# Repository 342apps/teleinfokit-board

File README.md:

# teleinfokit-board

## Firmware TeleInfoKit

Ce repo comprend les fichiers source Eagle, schema et PCB pour le module de collecte de tele-information [Teleinfokit](https://342apps.net/module-teleinfokit/) associé à son [firmware dédié](https://github.com/342apps/teleinfokit).

Ce module permet de récupérer les données de consommation électrique grâce aux données de télé-information du bus TIC des compteurs électriques français et d'exploiter ces données dans une application de domotique telle que Home Assistant.

## Compatibilité avec ESPHome

Ce module est également compatible avec un firmware généré par [ESPHome](https://esphome.io/) pour une integration dans Home Assistant. 

Le fichier de configuration compatible avec ce module ainsi que toute la documentation est disponible dans le dossier [esphome](./esphome/). Ce firmware offre cependant moins de fonctionnalités que le firmware natif.

## PCB

Fichier source [schematics Eagle](eagle/v4/schematics.sch)

Les versions hardware 3 et 4 sont disponibles dans leurs [répertoires dédiés](/eagle/).

### Gerber files

Toutes les ressources de production générées par Eagle sont dans le dossier [CAMOutputs](CAMOutputs).

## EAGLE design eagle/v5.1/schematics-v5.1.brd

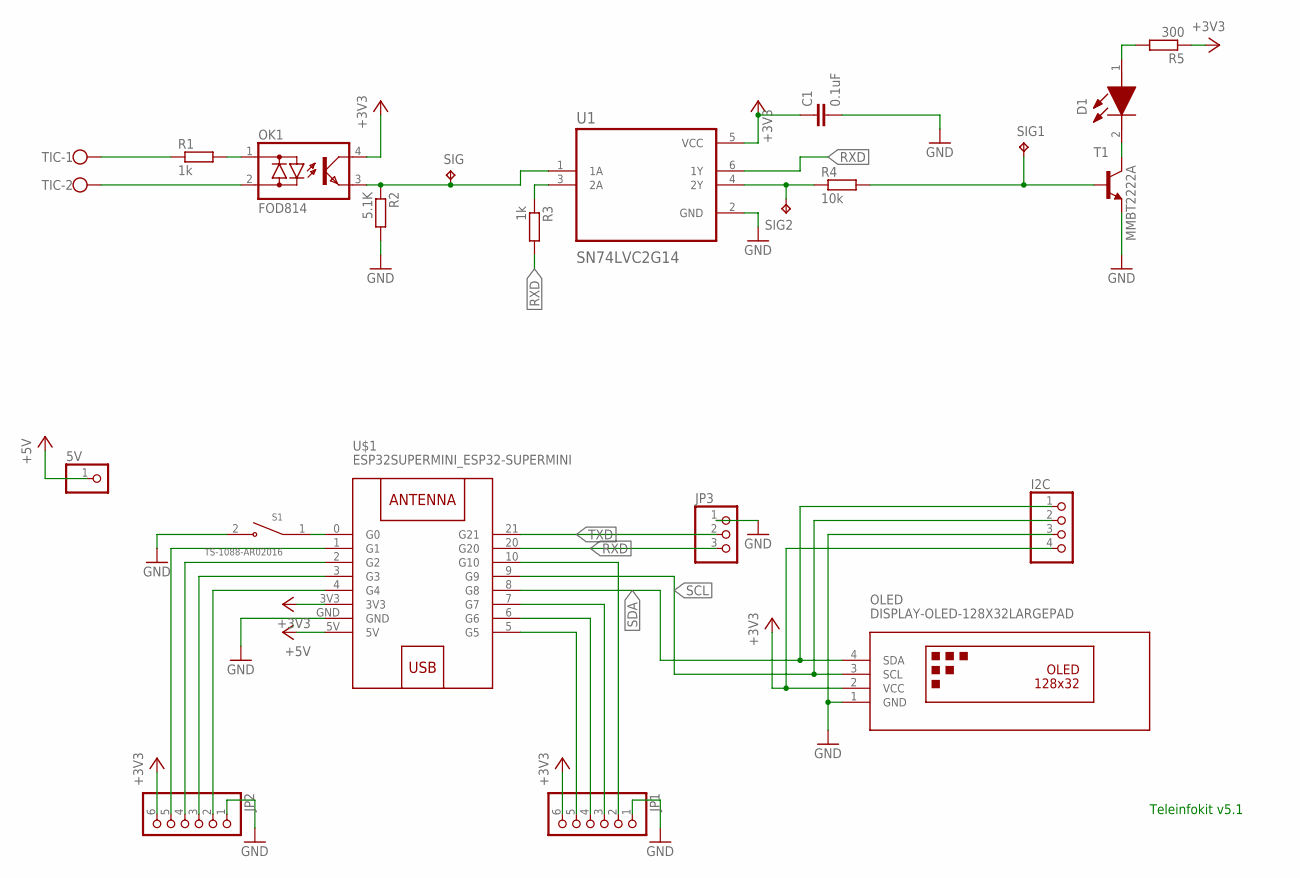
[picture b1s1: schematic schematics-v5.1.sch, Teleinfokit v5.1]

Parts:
5V: PINHD-1X1; 1X01
C1: 0.1uF; C0402K; LCSC_PART C1525
D1: 17-21SURC_S530-A2_TR8; 1721SURCS530A2TR8
I2C: PINHD-1X4ROUNDLARGE; 1X04ROUNDLARGE
JP1, JP2: PINHD-1X6CB; 1X06-CLEANBIG
JP3: PINHD-1X3; 1X03
OK1: FOD814; DIL4-SMD; LCSC_PART C479718
OLED: DISPLAY-OLED-128X32LARGEPAD; DISPLAY-OLED-128X32LARGE; LCSC_PART C2718488
R1: 1k; R0805; LCSC_PART C17513
R2: 5.1K; R0603; LCSC_PART C23186
R3: 1k; R0805; LCSC_PART C17414
R4: 10k; R0805; LCSC_PART C17414
R5: 300; R0805; LCSC_PART C17617
S1: TS-1088-AR02016; SW_TS-1088-AR02016; LCSC_PART C720477
SIG, SIG1, SIG2: TPB1,27; B1,27
T1: MMBT2222A; SOT23-BEC; LCSC_PART C8512
TIC: W237-102
U1: SN74LVC2G14; SOT95P280X145-6N; LCSC_PART C12401
U$1: ESP32SUPERMINI_ESP32-SUPERMINI

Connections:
+3V3: C1.1, I2C.4, JP1.6, JP2.6, OK1.4 (C), OLED.2 (VCC), R5.1, U1.5 (VCC), U$1.3V3
+5V: 5V.1, U$1.5V
GND: C1.2, I2C.3, JP1.1, JP2.1, JP3.1, OLED.1 (GND), R2.2, S1.2, T1.E, U1.2 (GND), U$1.GND
IO1: JP2.5, U$1.1 (G1)
IO2: JP2.4, U$1.2 (G2)
IO3: JP2.3, U$1.3 (G3)
IO4: JP2.2, U$1.4 (G4)
IO5: JP1.5, U$1.5 (G5)
IO6: JP1.4, U$1.6 (G6)
IO7: JP1.3, U$1.7 (G7)
IO10: JP1.2, U$1.10 (G10)
unnamed: OK1.1 (AC1), R1.2
unnamed: D1.1 (A), R5.2
unnamed: R4.1, SIG2.TP, U1.4 (2Y)
unnamed: R1.1, TIC.1
unnamed: OK1.2 (AC2), TIC.2
unnamed: OK1.3 (E), R2.1, SIG.TP, U1.1 (1A)
unnamed: D1.2 (K), T1.C
unnamed: R4.2, SIG1.TP, T1.B
unnamed: R3.1, U1.3 (2A)
unnamed: S1.1, U$1.0 (G0)
RXD: JP3.3, R3.2, U1.6 (1Y), U$1.20 (G20)
SCL: I2C.2, OLED.3 (SCL), U$1.9 (G9)
SDA: I2C.1, OLED.4 (SDA), U$1.8 (G8)
TXD: JP3.2, U$1.21 (G21)

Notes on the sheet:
Teleinfokit v5.1

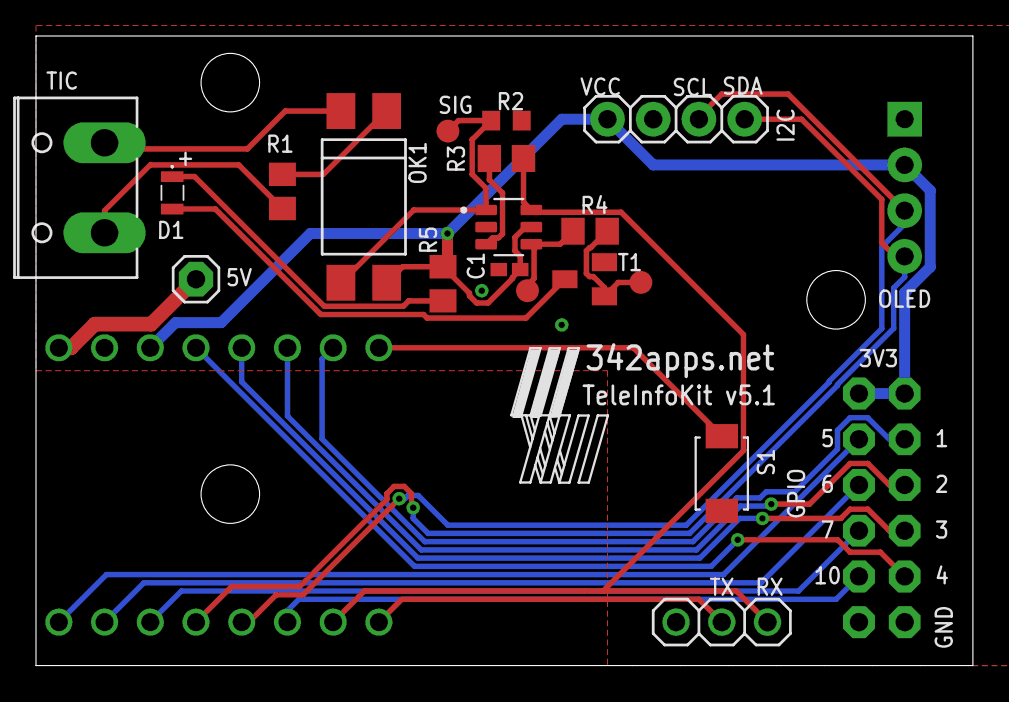
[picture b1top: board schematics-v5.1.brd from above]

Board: 2 copper layers, 52.0 x 35.0 mm, 22 parts (0 on the bottom side), 25 nets.

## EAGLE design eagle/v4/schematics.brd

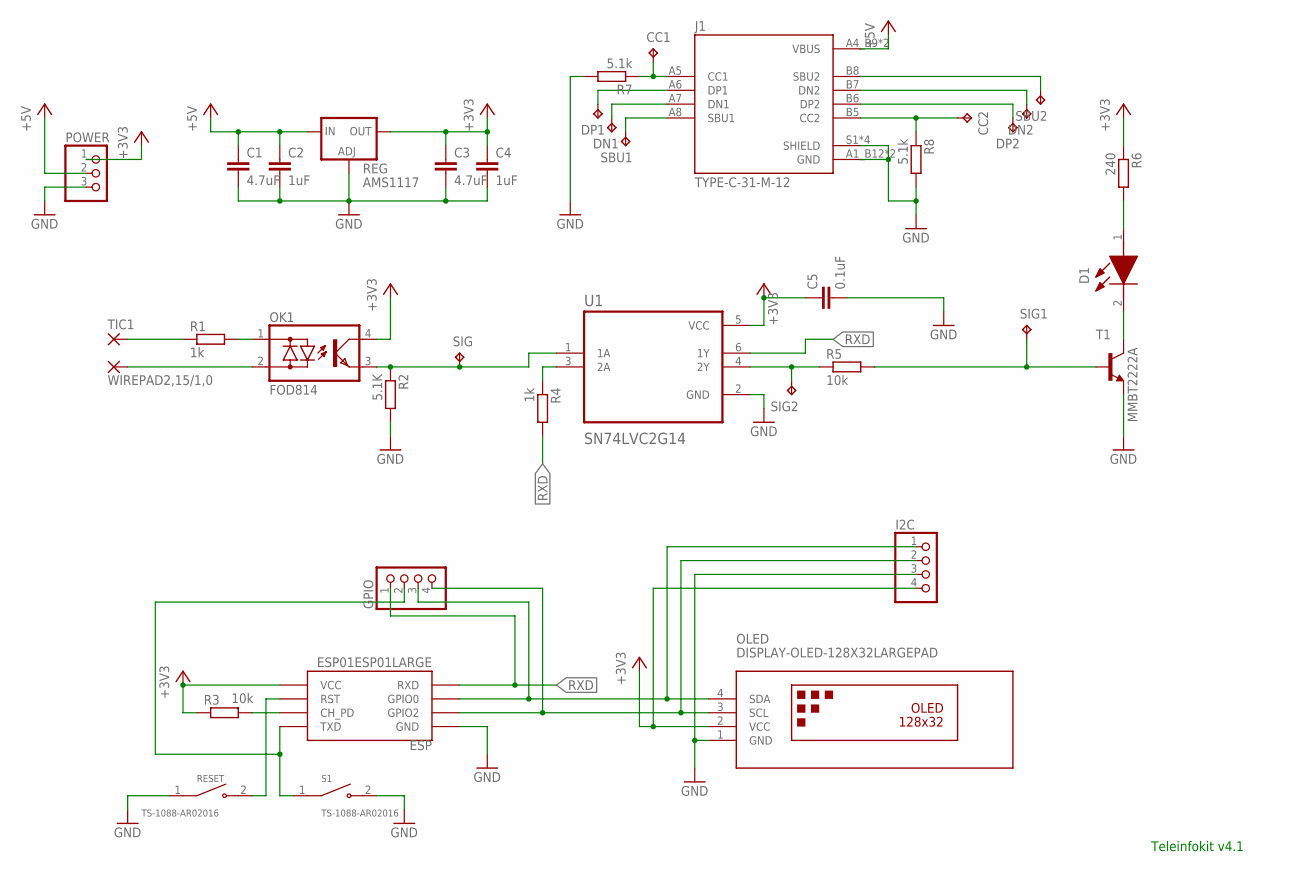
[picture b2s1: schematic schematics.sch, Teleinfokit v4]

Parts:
C1, C3: 4.7uF; C0805; LCSC_PART C1779
C2, C4: 1uF; C0805; LCSC_PART C28323
C5: 0.1uF; C0402K; LCSC_PART C1525
CC1, CC2: TPB1,27; B1,27
D1: 17-21SURC_S530-A2_TR8; 1721SURCS530A2TR8
DN1, DN2: TPB1,27; B1,27
DP1, DP2: TPB1,27; B1,27
ESP: ESP01ESP01LARGE; ESP01LARGE; LCSC_PART C2935984
GPIO: PINHD-1X4; 1X04
I2C: PINHD-1X4ROUNDLARGE; 1X04ROUNDLARGE
J1: TYPE-C-31-M-12; HRO_TYPE-C-31-M-12; LCSC_PART C165948
OK1: FOD814; DIL04; LCSC_PART C479718
OLED: DISPLAY-OLED-128X32LARGEPAD; DISPLAY-OLED-128X32LARGE; LCSC_PART C2718488
POWER: PINHD-1X3; 1X03
R1: 1k; R0805; LCSC_PART C17513
R2: 5.1K; R0805; LCSC_PART C17414
R3, R5: 10k; R0805; LCSC_PART C17414
R4: 1k; R0805; LCSC_PART C17414
R6: 240; R0805; LCSC_PART C17572
R7, R8: 5.1k; R0402; LCSC_PART C25905
REG: AMS1117; SOT223; LCSC_PART C6186
RESET: TS-1088-AR02016; SW_TS-1088-AR02016; LCSC_PART C720477
S1: TS-1088-AR02016; SW_TS-1088-AR02016; LCSC_PART C720477
SBU1, SBU2: TPB1,27; B1,27
SIG, SIG1, SIG2: TPB1,27; B1,27
T1: MMBT2222A; SOT23-BEC; LCSC_PART C8512
TIC1, TIC2: WIREPAD2,15/1,0; 2,15/1,0
U1: SN74LVC2G14; SOT95P280X145-6N; LCSC_PART C12401

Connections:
+3V3: C3.1, C4.1, C5.1, ESP.VCC, I2C.4, OK1.4 (C), OLED.2 (VCC), POWER.1, R3.1, R6.1, REG.4 (OUT), U1.5 (VCC)
+5V: C1.1, C2.1, J1.A4_B9 (VBUS), J1.B4_A9 (VBUS), POWER.2, REG.3 (IN)
GND: C1.2, C2.2, C3.2, C4.2, C5.2, ESP.GND, I2C.3, J1.A1_B12 (GND), J1.B1_A12 (GND), J1.S1 (SHIELD), J1.S2 (SHIELD), J1.S3 (SHIELD), J1.S4 (SHIELD), OLED.1 (GND), POWER.3, R2.2, R7.2, R8.2, REG.1 (ADJ), RESET.1, S1.2, T1.E, U1.2 (GND)
unnamed: OK1.1 (AC1), R1.2
unnamed: ESP.GPIO0, GPIO.3, I2C.1, OLED.4 (SDA)
unnamed: D1.1 (A), R6.2
unnamed: ESP.TX (TXD), GPIO.2, S1.1
unnamed: R5.1, SIG2.TP, U1.4 (2Y)
unnamed: ESP.GPIO2, GPIO.4, I2C.2, OLED.3 (SCL)
unnamed: R1.1, TIC1.1
unnamed: OK1.2 (AC2), TIC2.1
unnamed: ESP.CH_PD, R3.2
unnamed: ESP.RST, RESET.2
unnamed: OK1.3 (E), R2.1, SIG.TP, U1.1 (1A)
unnamed: D1.2 (K), T1.C
unnamed: R5.2, SIG1.TP, T1.B
unnamed: CC1.TP, J1.A5 (CC1), R7.1
unnamed: R4.1, U1.3 (2A)
unnamed: CC2.TP, J1.B5 (CC2), R8.1
unnamed: DP1.TP, J1.A6 (DP1)
unnamed: DN1.TP, J1.A7 (DN1)
unnamed: J1.A8 (SBU1), SBU1.TP
unnamed: J1.B8 (SBU2), SBU2.TP
unnamed: DN2.TP, J1.B7 (DN2)
unnamed: DP2.TP, J1.B6 (DP2)
RXD: ESP.RX (RXD), GPIO.1, R4.2, U1.6 (1Y)

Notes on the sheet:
Teleinfokit v4.1

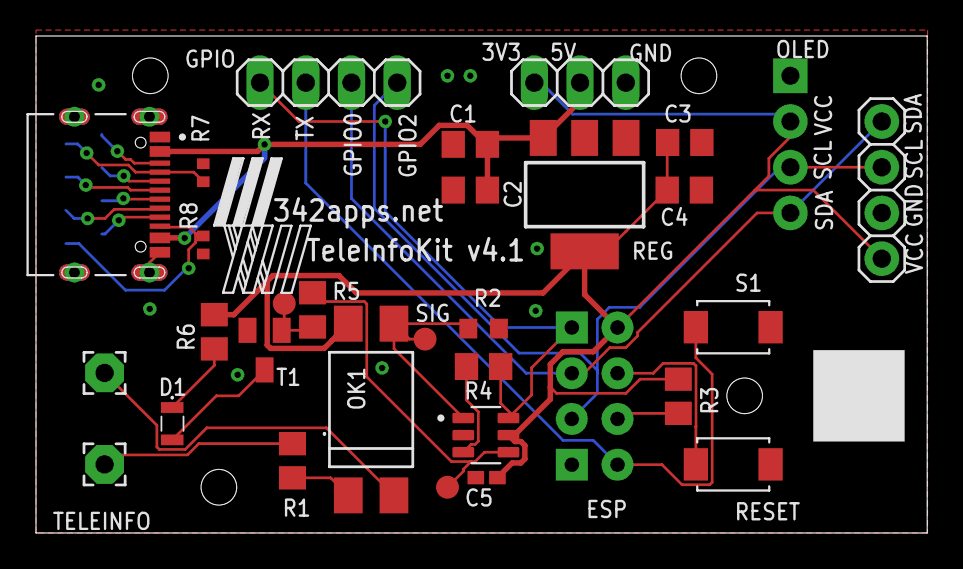
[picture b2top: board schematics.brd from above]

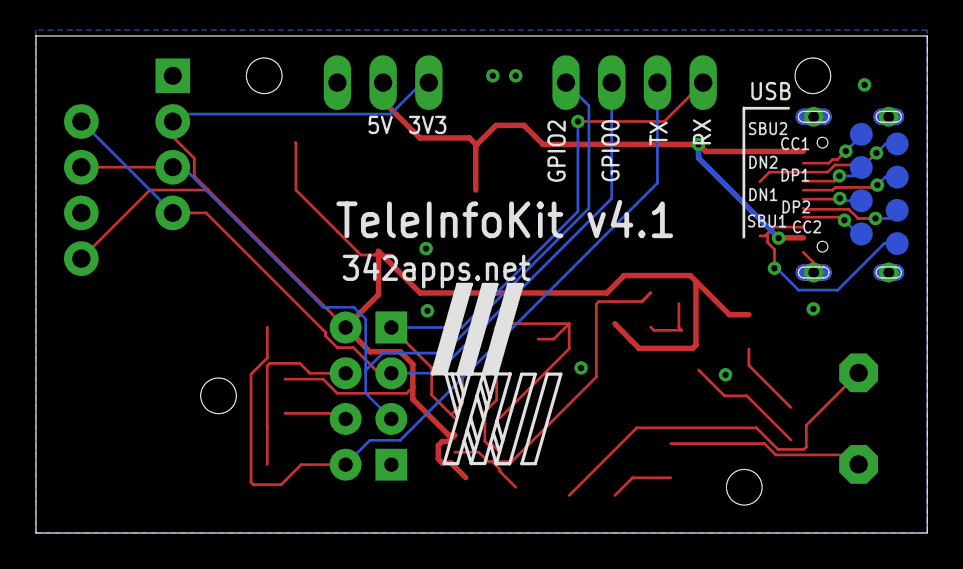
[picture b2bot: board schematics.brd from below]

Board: 2 copper layers, 49.5 x 27.6 mm, 39 parts (8 on the bottom side), 26 nets.

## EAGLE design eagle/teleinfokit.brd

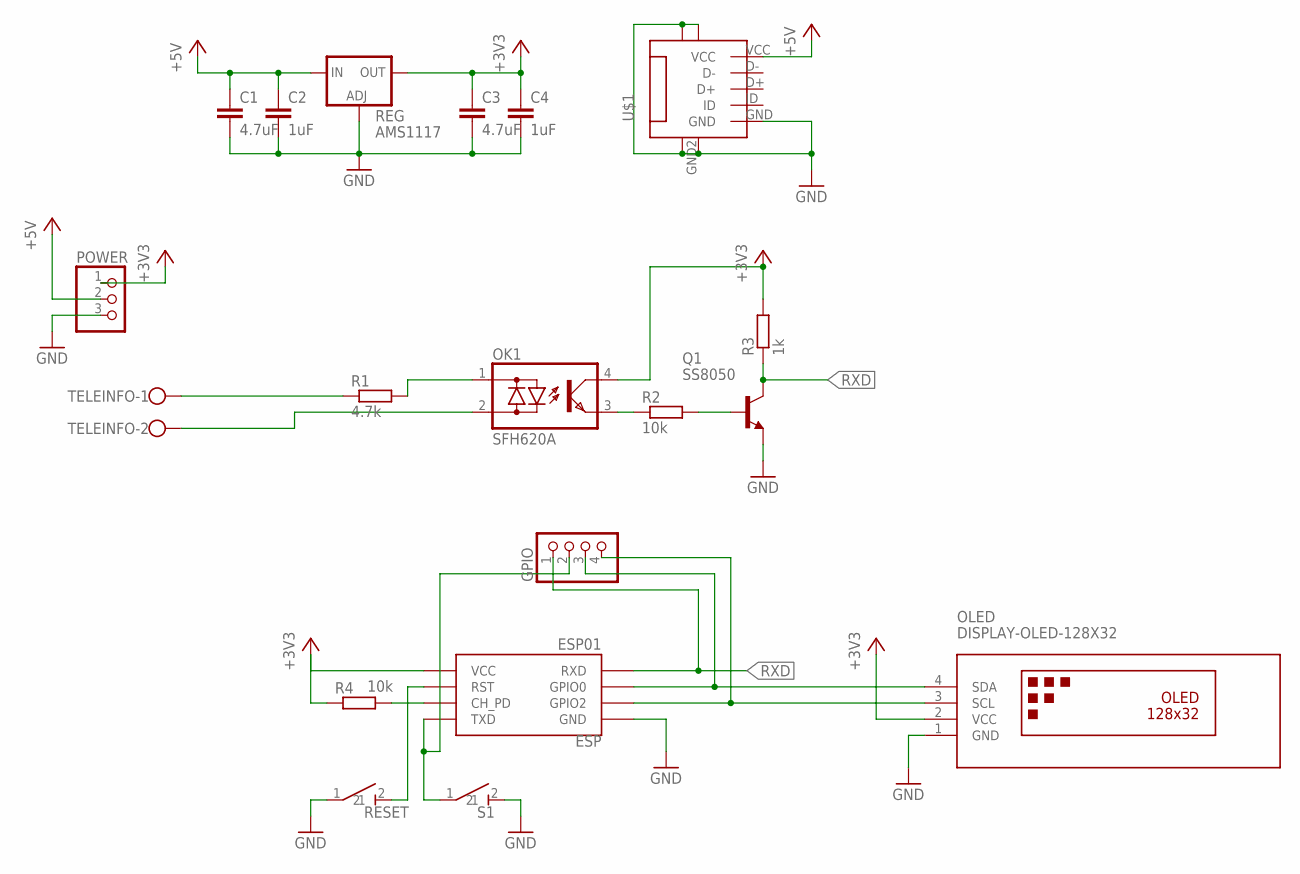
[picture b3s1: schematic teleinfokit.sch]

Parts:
C1, C3: 4.7uF; C0805; LCSC_PART C1779
C2, C4: 1uF; C0805; LCSC_PART C28323
ESP: ESP01
GPIO: PINHD-1X4; 1X04
OK1: SFH620A; DIL04
OLED: DISPLAY-OLED-128X32
POWER: PINHD-1X3; 1X03
Q1: SS8050; SOT23-BEC; LCSC_PART C2150
R1: 4.7k; R0805; LCSC_PART C17673
R2, R4: 10k; R0805; LCSC_PART C17414
R3: 1k; R0805; LCSC_PART C17513
REG: AMS1117; SOT223; LCSC_PART C6186
RESET: MICROSWITCH
S1: MICROSWITCH
TELEINFO: W237-102
U$1: USB_MICRO_SMD; LCSC_PART C145783

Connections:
+3V3: C3.1, C4.1, ESP.VCC, OK1.4 (C), OLED.2 (VCC), POWER.1, R3.2, R4.1, REG.4 (OUT)
+5V: C1.1, C2.1, POWER.2, REG.3 (IN), U$1.VCC
GND: C1.2, C2.2, C3.2, C4.2, ESP.GND, OLED.1 (GND), POWER.3, Q1.E, REG.1 (ADJ), RESET.1, S1.2, U$1.GND, U$1.GND1, U$1.GND2, U$1.GND3, U$1.GND4
unnamed: OK1.1 (AC1), R1.2
unnamed: ESP.GPIO0, GPIO.3, OLED.4 (SDA)
unnamed: ESP.TX (TXD), GPIO.2, S1.1
unnamed: Q1.B, R2.2
unnamed: ESP.GPIO2, GPIO.4, OLED.3 (SCL)
unnamed: R1.1, TELEINFO.1
unnamed: OK1.2 (AC2), TELEINFO.2
unnamed: ESP.CH_PD, R4.2
unnamed: ESP.RST, RESET.2
unnamed: OK1.3 (E), R2.1
RXD: ESP.RX (RXD), GPIO.1, Q1.C, R3.1

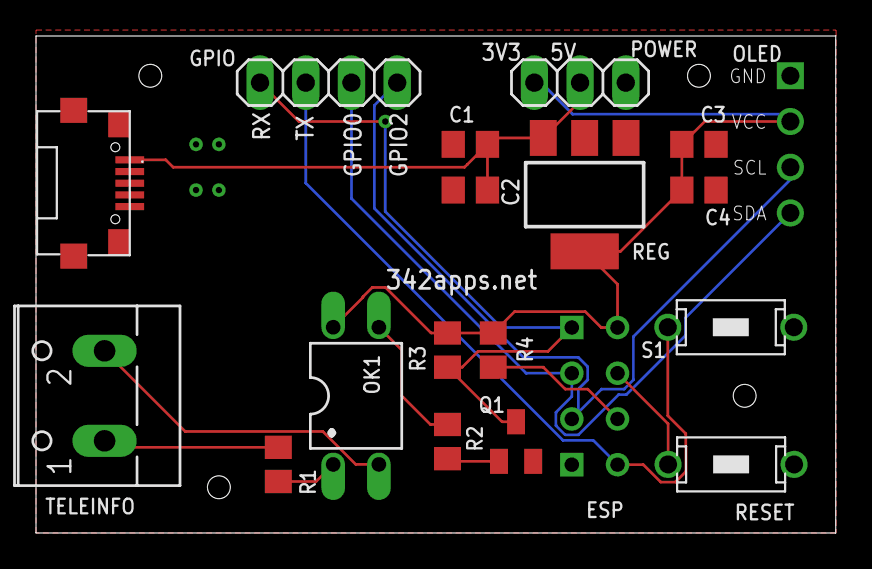
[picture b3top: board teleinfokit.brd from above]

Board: 2 copper layers, 44.4 x 27.6 mm, 19 parts (0 on the bottom side), 14 nets.

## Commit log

2021-04-28 Added board resources
2021-04-28 Added gerber files
2021-05-03 Add esphome config file
2021-05-03 turn screen on and off with button
2021-05-03 Update documentation
2021-05-10 Added 3d models
2021-07-17 Update ESPHome configuration
2021-07-19 ESPHome: update names
    Some little changes:
    * Not necessary to add ESPHome to Teleinfokit as it is for the same project;
    * Not sure of the behavior of a Wifi access point with a space inside so also change it and use an underscor
2021-07-20 Add intensity to the esphome config file
2021-07-28 Improve ESPHome firmware
    * Use secrets.yaml to store sensitive data
    * Change sensors name to have them in French
    * Add a documentation to list secret.yaml values and give some tips
2021-08-01 Add classes to sensors
    * State class to specify it is a measurement sensor
    * device_class to specify it is an energy sensor
    After more configuration on Home-Assistant side, it could allow to use these sensors with energy integration from Home-Assistant 2021.8
2021-08-21 Update README.md
    orthographe et six caractère
2021-08-21 Update README.md
    fix orthographe et guillemet dans la doc
2021-08-24 Mark the teleinfokit_switch binary sensor internal
    As it is used for the physical button, it is not needed to display it for API
    Note: for existting installations in Home Assistant, it will make the previously added entity as orphan and the Delete button looks unavailable.
2021-08-26 Convert sensors data to kWh
    It makes integration easyer to Home Assistant energy dashboard, avoiding to create template sensors in Home Assistant where conversion would be made.
    In this way utility meters can be directly sourced by ESPHome sensors.
    Decimals are displayed to have the most precize measures.
2021-08-27 Do not apply fiter on the display device
2021-09-06 Add ESPHome configuration file for use with BMP280
2021-09-07 Add classes to directly integrate sensors to HA energy dashboard
2021-09-16 Add DS_Store to gitignore
2021-09-16 Homogeneize hotspot and password with native firmware
2021-09-24 Appy last changes to example with bmp sensor
2021-09-26 Change filter in kWh conversion
    I forgot to submit something in #6 when converting to kWh
    As multiply is native to ESPHome and has the same result we have now, there is no reason to use a lambda filter.
2021-09-26 Also update BMP280 ESPHome firmware
2021-12-02 Fichier de configuration pour modules sans écran
2022-05-05 Ajout affichage index base
2022-06-14 Add off_on_boot substitution variable to be able to switch screen off on boot
    Do not update screen when it is switched off
2024-03-17 Add standard config files and update historic
2024-03-17 rename historic config file
2024-03-17 Add comments
2024-03-17 update gitignore
2024-03-17 Hardware for version 4
2025-01-26 HW4.1
2025-07-24 update v4
2025-07-24 HW V5.0
2025-07-24 V5 update
2025-08-06 Rename V4 files
2025-08-06 ignore schematics temp files
2026-02-24 hw 5.1 updates

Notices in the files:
parts and their libraries:
oled-edit: Released under the Creative Commons Attribution 4.0 International License: http://creativecommons.org/licenses/by/4.0
